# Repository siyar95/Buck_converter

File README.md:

# Adjustable Buck Converter – AP63301 (12V to 5V, 3A Max)

This project features a compact, high-efficiency **synchronous buck converter** utilizing the **AP63301** from Diodes Incorporated. It steps down a **12V input** to a **5V output**, delivering up to **3A** of continuous current.

## 🔧 Features

- **Input Voltage**: 3.8V to 32V (12V nominal)
- **Output Voltage**: Adjustable via external resistor divider (configured for 5V)
- **Maximum Output Current**: 3A continuous
- **Switching Frequency**: 500kHz
- **Efficiency**: Up to 88% at light loads

## 🧱 PCB Details

- 2-layer PCB design
- Output voltage set via resistor divider (e.g., 158kΩ and 30.1kΩ for 5V output)
- Inductor: 6.8μH recommended for 5V output at 3A load
- Input and output capacitors selected per datasheet recommendations for stability and performance

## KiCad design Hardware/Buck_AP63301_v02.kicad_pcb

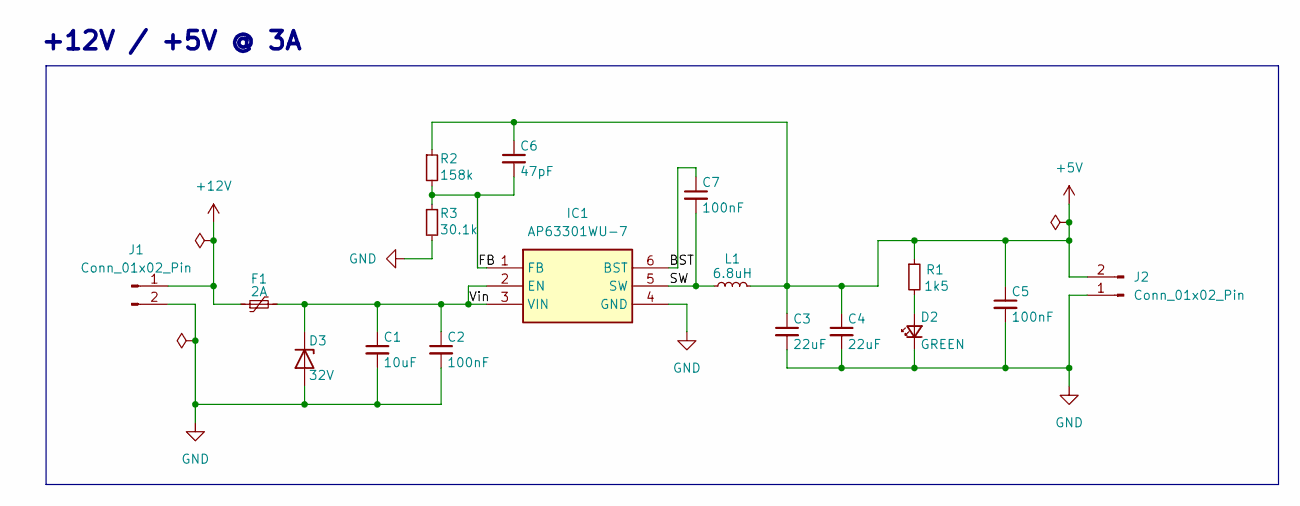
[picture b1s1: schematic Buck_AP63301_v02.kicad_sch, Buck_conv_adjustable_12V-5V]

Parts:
C1: 10uF; C_1206_3216Metric
C2: 100nF; C_1206_3216Metric
C3, C4: 22uF; C_1206_3216Metric
C5, C7: 100nF; C_0603_1608Metric
C6: 47pF; C_0603_1608Metric
D2: GREEN; LED_0603_1608Metric
D3: 32V; Nexperia_DSN1608-2_1.6x0.8mm
F1: 2A; Fuse_1210_3225Metric
IC1: AP63301WU-7; AP63301; Mouser Part Number 621-AP63301WU-7
J1, J2: Conn_01x02_Pin; PinHeader_1x02_P2.54mm_Vertical
L1: 6.8uH; L_10.4x10.4_H4.8
R1: 1k5; R_0603_1608Metric
R2: 158k; R_0603_1608Metric
R3: 30.1k; R_0603_1608Metric

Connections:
+5V: C3.1, C4.1, C5.1, C6.1, J2.2, L1.2, R1.1, R2.1
+12V: F1.1, J1.1
/BST: C7.1, IC1.6 (BST)
/FB: C6.2, IC1.1 (FB), R2.2, R3.1
/SW: C7.2, IC1.5 (SW), L1.1
/Vin: C1.1, C2.1, D3.1 (K), F1.2, IC1.2 (EN), IC1.3 (VIN)
GND: C1.2, C2.2, C3.2, C4.2, C5.2, D2.1 (K), D3.2 (A), IC1.4 (GND), J1.2, J2.1, R3.2
unnamed: D2.2 (A), R1.2

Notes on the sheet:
+12V / +5V @ 3A

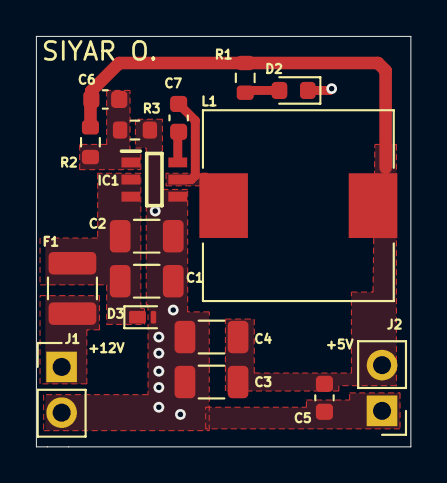
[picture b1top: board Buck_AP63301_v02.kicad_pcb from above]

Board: 2 copper layers, 20.8 x 22.8 mm, 17 parts (0 on the bottom side), 8 nets.

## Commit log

2025-05-06 Rename Buck_AP63301_v02.kicad_pro to Hardware/Buck_AP63301_v02.kicad_pro
